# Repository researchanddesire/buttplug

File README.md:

# Buttplug Compass

[Read the illustrated engineering and assembly docs](https://researchanddesire.github.io/buttplug/)

For AJ and other collaborators: start with [the checkpoint handoff](COLLABORATION.md).
It distinguishes the saved threaded-stub CAD from unresolved locking/tooling choices.

Compass is a smart plug and charging dock. The device is a turned stainless
steel body and nose cap with a cast silicone flange. One 52 × 20 mm board in the
flange carries the ESP32-C3, charger, motor driver, temperature sensing and
compass. A protected LiPo and the vibration motor sit in the bulb. The clamshell
dock charges it through four contacts, connects it to a computer over USB, and
has a screen, three buttons and UV-C LEDs.

**Status:** EVT1 design in CAD and KiCad. The current device and dock still
need assembly and bench commissioning. See [Project status](developer-docs/docs/status.md).

| Start here | |
| --- | --- |
| How the device works | [developer-docs/docs/device.md](developer-docs/docs/device.md) |
| Step-by-step assembly | [assembly-docs/assembly-guide.md](assembly-docs/assembly-guide.md) |
| Metal part drawings | [developer-docs/docs/drawings.md](developer-docs/docs/drawings.md) |
| Charging dock | [developer-docs/docs/charging-dock.md](developer-docs/docs/charging-dock.md) |
| Device CAD (FreeCAD scripts, STEP) | [hardware/pcb/evt1/one-board/mech/](https://github.com/researchanddesire/buttplug/blob/backplane/trial/hardware/pcb/evt1/one-board/mech/README.md) |
| Device board (KiCad) | [hardware/pcb/evt1/one-board/](https://github.com/researchanddesire/buttplug/blob/backplane/trial/hardware/pcb/evt1/one-board/README.md) |
| Dock CAD | [hardware/cad/evt1-assembly/evt1-wired/](https://github.com/researchanddesire/buttplug/blob/backplane/trial/hardware/cad/evt1-assembly/evt1-wired/README.md) |
| Firmware | [developer-docs/docs/firmware.md](developer-docs/docs/firmware.md) |
| Requirements | [developer-docs/docs/prd.md](developer-docs/docs/prd.md) |
| Human-owned BOM | [hardware/bom.csv](hardware/bom.csv) |

Use Git history and [archived studies](developer-docs/docs/archive/index.md)
for earlier work.
The docs build automatically when changes land on `main`. See [developer site setup](developer-docs/README.md).

Forked from [researchanddesire/rad-project-template](https://github.com/researchanddesire/rad-project-template).
Repository: `researchanddesire/buttplug`; the local folder keeps its earlier name.
Product release and license selection remain pending. See [LICENSE](LICENSE).

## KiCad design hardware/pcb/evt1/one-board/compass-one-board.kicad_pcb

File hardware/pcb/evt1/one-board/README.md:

# Compass EVT1 device

The compact, four-layer device PCB is 52 × 20 × 1 mm and populated on
both sides. Open [the KiCad project](compass-one-board.kicad_pro) to view the
charger, motor driver, ESP32-C3, sensors, buttons and four dock contacts.
The [FreeCAD assembly](mech/compass-device.FCStd) puts the PCB in a
56 × 32 mm rigid flange and the pack in a removable cradle in the bulb.
Keep the linked parts in the [mechanical source directory](mech/README.md).

| Connector | Function |
| --- | --- |
| J2 | Three-wire protected pack, JST SH. Pins 1 P+, 2 P−, 3 NTC |
| J3 | Motor pair, side-entry JST SH |
| J4 | Bench service and recovery, JST SH |
| J5 | Tip NTC pair, side-entry JST SH |
| CT1–CT4 | Dock GND, D−, D+ and 5 V |

The [BC-PACK-EVT1-002 request](PACK-RFQ.md) calls for one internal 10 kΩ B3435
NTC returned to P−. It feeds the BQ24074 charge-temperature cutoff and U7 AIN2.
The `evt1-one-board` firmware target still uses the former pulsed-divider
acquisition and conversion for AIN2. The shared charger-biased reading
needs implementation and bench validation. The 1 A JST SH rating also needs
reconciliation with the requested 1.5 A continuous pack load.

The [harness sources](../../../cables/evt1/one-board/README.md) define the seven
installed conductors and a separate bench service cable. Their starting stock
lengths come from the CAD wire paths. Check bend radii, crimp retention and
fit on the trial build.

See the [developer and assembly site](https://researchanddesire.github.io/buttplug/)
for the construction drawings, seal sections, assembly sequence and bring-up
plan. Some FreeCAD generation scripts still assume the original checkout path.
The saved native can be opened with its relative part links in place.
The PCB STEP is the mechanical integration model from before the last layout
edits. The compact assembly, mating interface and charging path still need
physical qualification before a fabrication release.

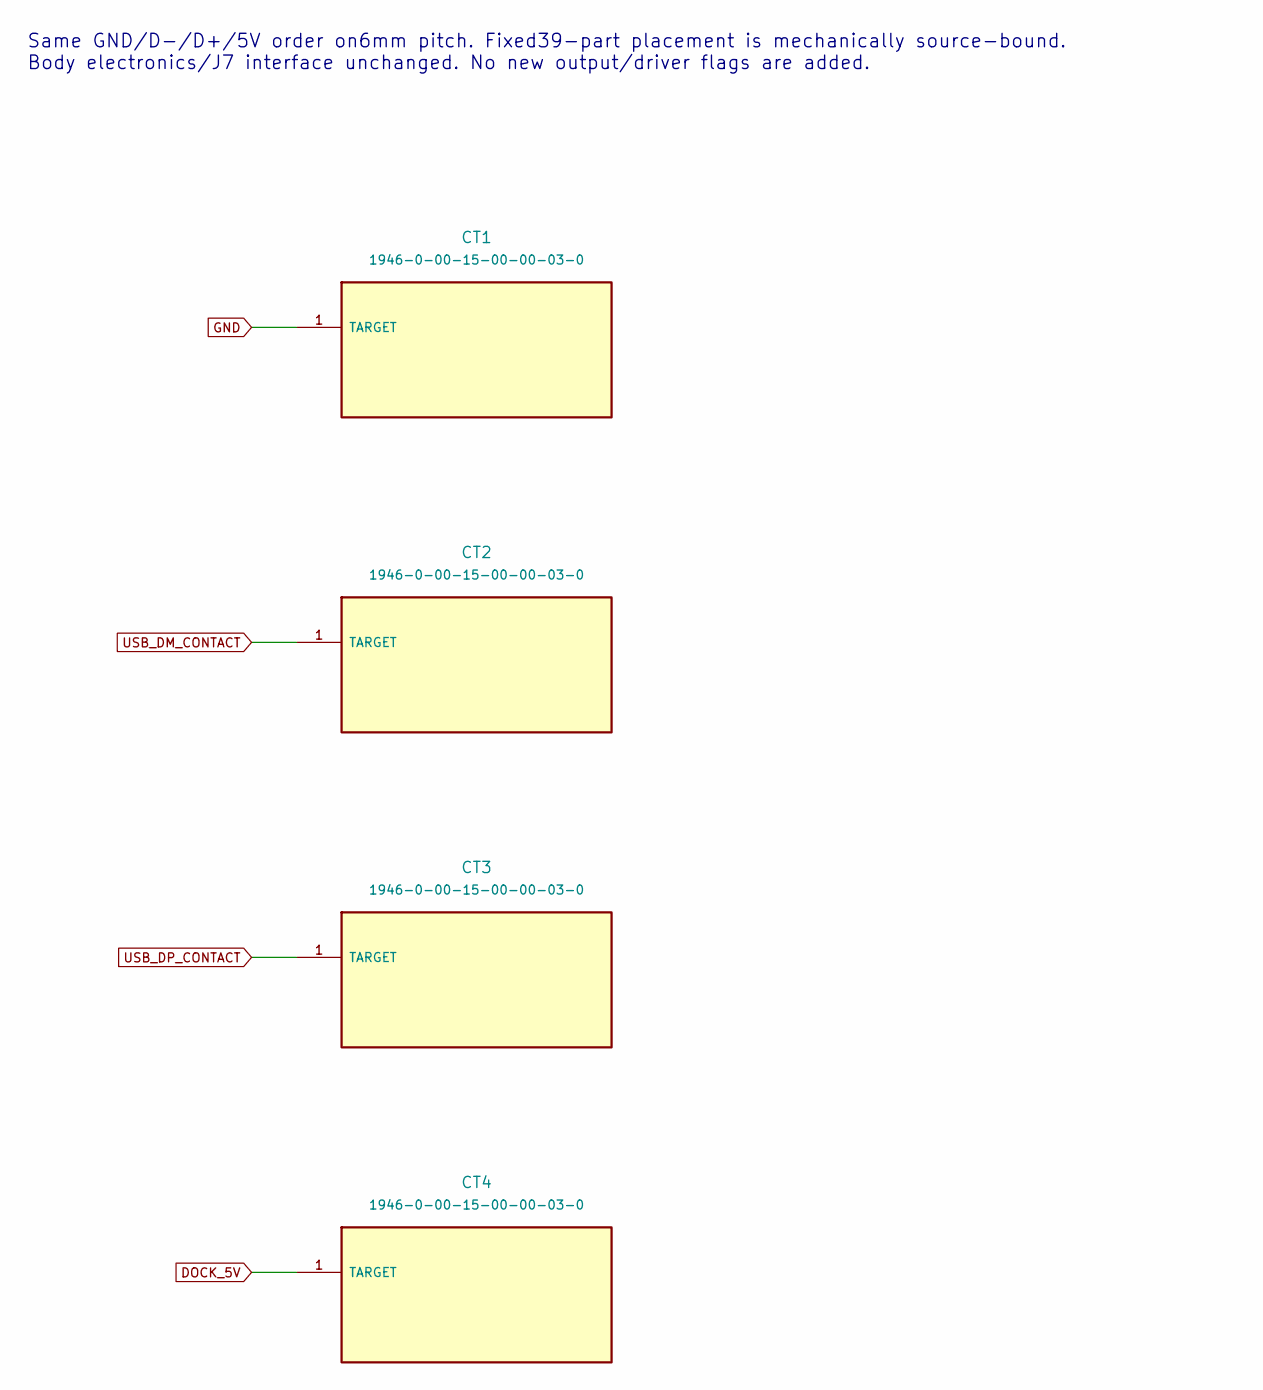
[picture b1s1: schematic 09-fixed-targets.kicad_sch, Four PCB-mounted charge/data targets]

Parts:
CT1, CT2, CT3, CT4: 1946-0-00-15-00-00-03-0; MillMax_1946_0_PTH_Study

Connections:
DOCK_5V: CT4.1; also elsewhere on the board
GND: CT1.1; also elsewhere on the board
USB_DM_CONTACT: CT2.1; also elsewhere on the board
USB_DP_CONTACT: CT3.1; also elsewhere on the board

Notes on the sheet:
Same GND/D−/D+/5V order on6mm pitch. Fixed39-part placement is mechanically source-bound. Body electronics/J7 interface unchanged. No new output/driver flags are added.

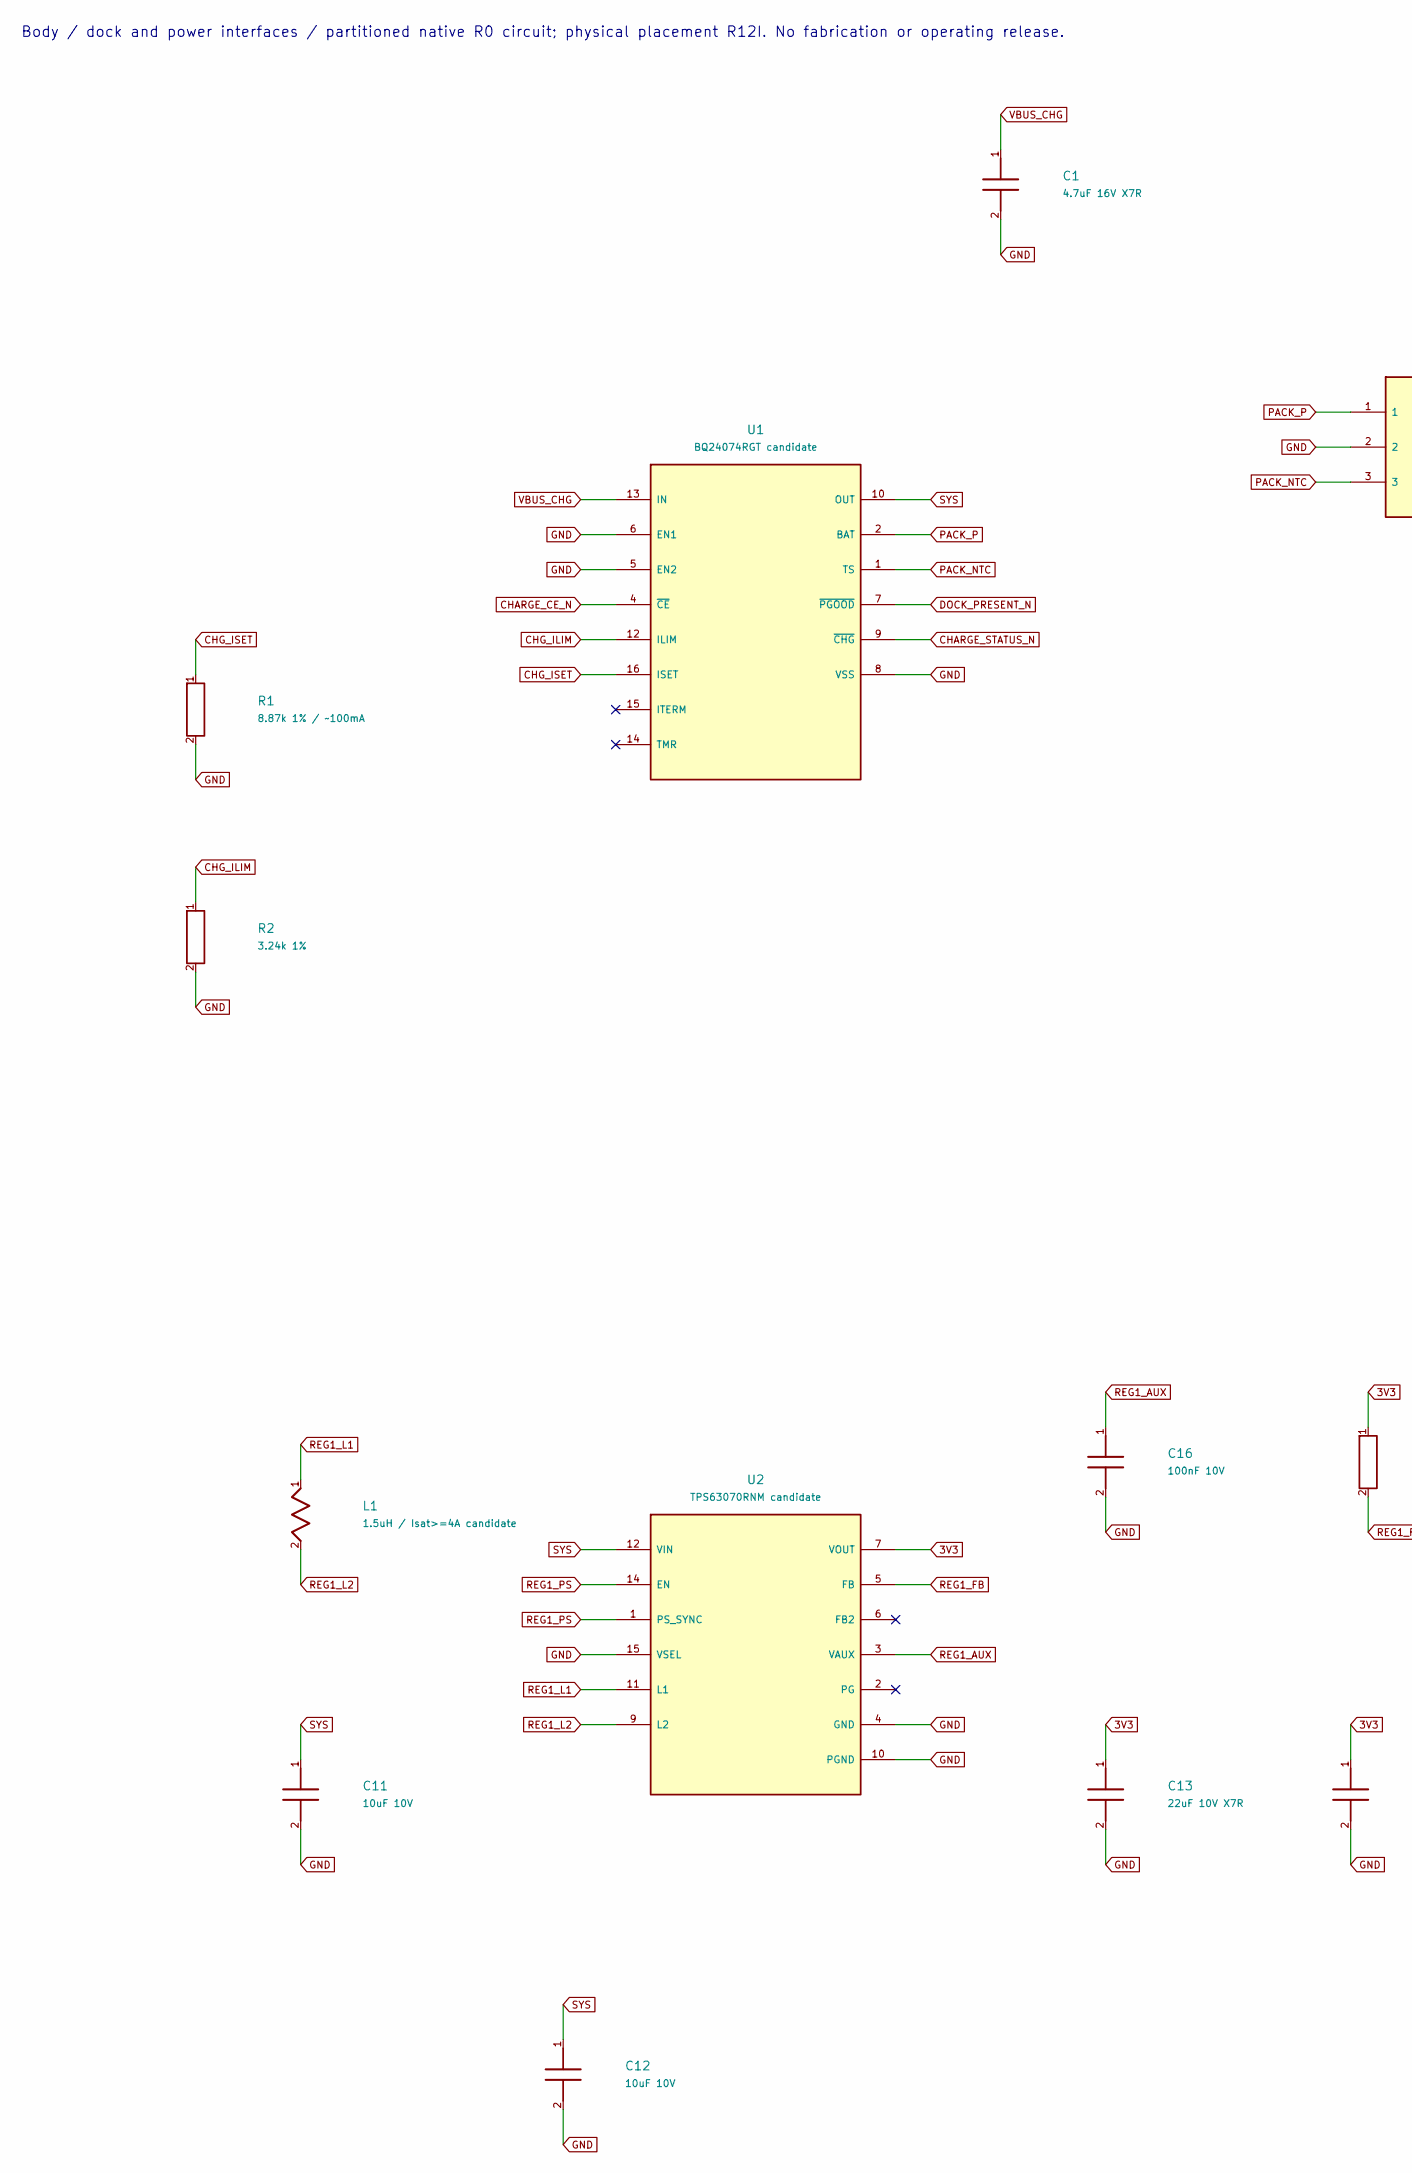
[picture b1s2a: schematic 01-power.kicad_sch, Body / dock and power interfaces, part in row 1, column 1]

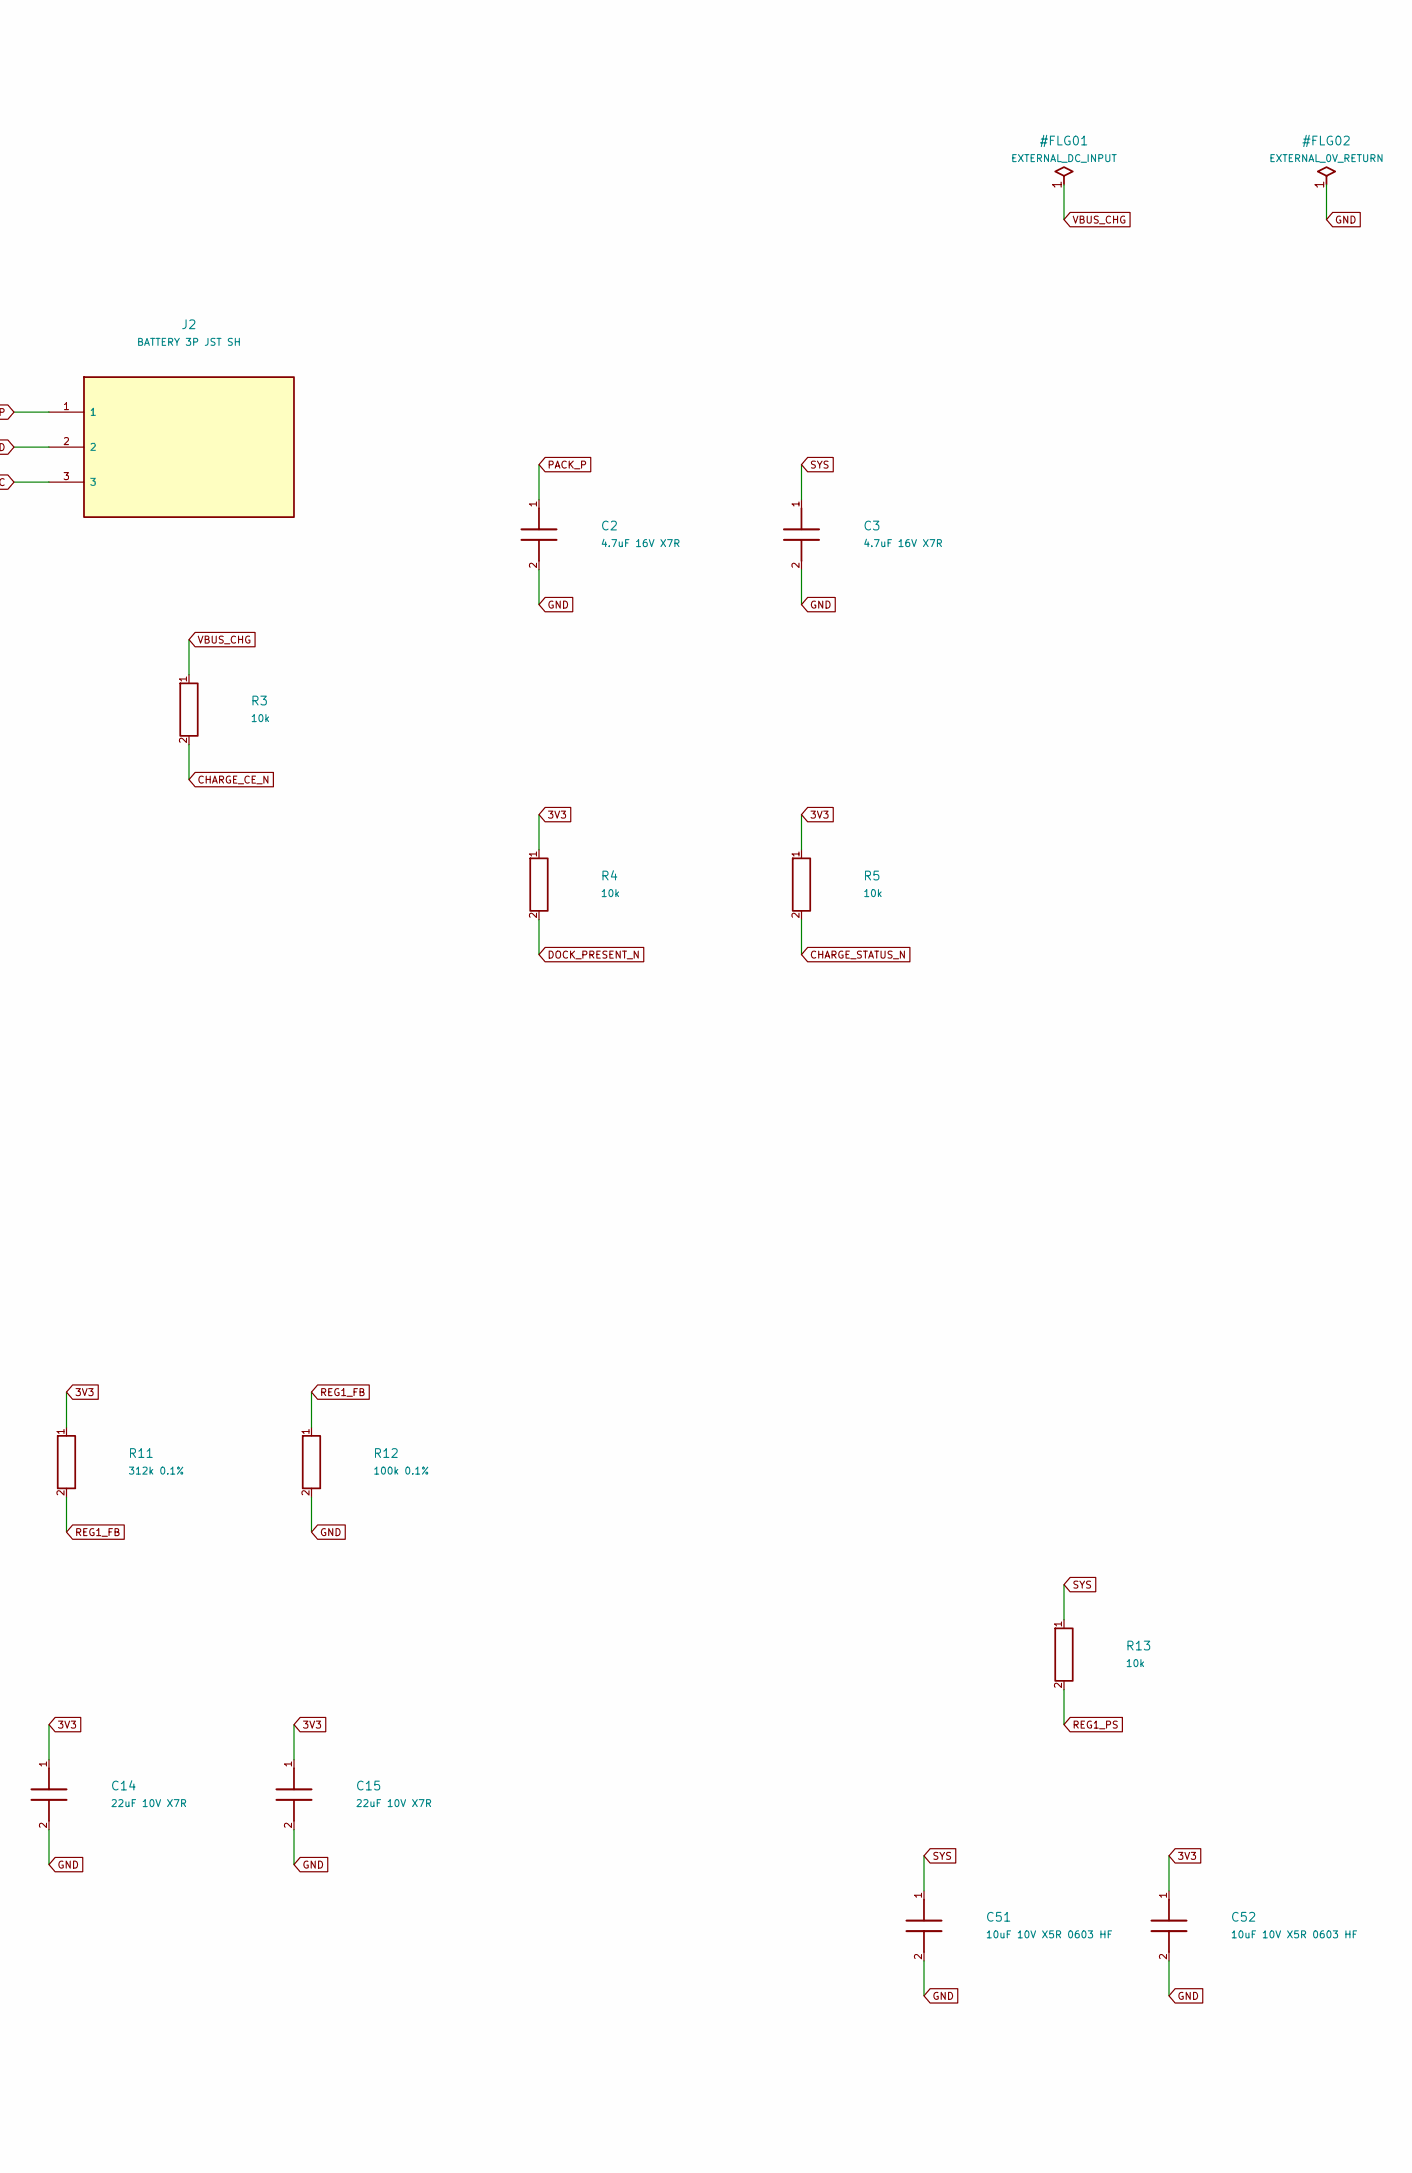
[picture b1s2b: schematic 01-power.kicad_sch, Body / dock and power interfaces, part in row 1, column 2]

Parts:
C1, C2, C3: 4.7uF 16V X7R; Murata_GRM21_0805_Reflow; Manufacturer Part Number GRM21BR71C475KE51L; LCSC Part Number C408144
C11, C12: 10uF 10V; Murata_GRM21_0805_Reflow
C13, C14, C15: 22uF 10V X7R; Murata_GRM31_1206_Reflow
C16: 100nF 10V; Murata_GRM18_0603_Reflow
C51, C52: 10uF 10V X5R 0603 HF; TDK_C1608_0603_Reflow; Manufacturer Part Number CL10A106KP8NNNC; LCSC Part Number C19702
J2: BATTERY 3P JST SH; JST_SH_SM03B-SRSS-TB_1x03-1MP_P1.00mm_Horizontal; Manufacturer Part Number SM03B-SRSS-TB(LF)(SN); LCSC Part Number C160403
L1: 1.5uH / Isat>=4A candidate; L_Coilcraft_XxL4020
R1: 8.87k 1% / ~100mA; R_0402_1005Metric; Manufacturer Part Number TC0210B8871TCC; LCSC Part Number C517790
R2: 3.24k 1%; R_0402_1005Metric; Manufacturer Part Number RT0402BRD073K24L; LCSC Part Number C852760
R3, R4, R5: 10k; R_0402_1005Metric
R11: 312k 0.1%; Vishay_TNPW0603_IEC_Reflow; Manufacturer Part Number RT0603BRD07312KL; LCSC Part Number C861315
R12: 100k 0.1%; Vishay_TNPW0603_IEC_Reflow
R13: 10k; Vishay_TNPW0603_IEC_Reflow
U1: BQ24074RGT candidate; TI_RGT0016C_3x3mm_BQ24074_EP1.68mm
U2: TPS63070RNM candidate; TI_RNM0015A_2.5x3mm_TPS63070

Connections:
3V3: C13.1, C14.1, C15.1, C52.1, R4.1, R5.1, R11.1, U2.7 (VOUT), U2.8 (VOUT); also elsewhere on the board
CHARGE_CE_N: R3.2, U1.4 (~CE); also elsewhere on the board
CHARGE_STATUS_N: R5.2, U1.9 (~CHG)
CHG_ILIM: R2.1, U1.12 (ILIM)
CHG_ISET: R1.1, U1.16 (ISET)
DOCK_PRESENT_N: R4.2, U1.7 (~PGOOD); also elsewhere on the board
GND: C1.2, C2.2, C3.2, C11.2, C12.2, C13.2, C14.2, C15.2, C16.2, C51.2, C52.2, J2.2, R1.2, R2.2, R12.2, U1.5 (EN2), U1.6 (EN1), U1.8 (VSS), U1.17 (EP), U2.4 (GND), U2.10 (PGND), U2.15 (VSEL); also elsewhere on the board
PACK_NTC: J2.3, U1.1 (TS); also elsewhere on the board
PACK_P: C2.1, J2.1, U1.2 (BAT), U1.3 (BAT); also elsewhere on the board
REG1_AUX: C16.1, U2.3 (VAUX)
REG1_FB: R11.2, R12.1, U2.5 (FB)
REG1_L1: L1.1, U2.11 (L1)
REG1_L2: L1.2, U2.9 (L2)
REG1_PS: R13.2, U2.1 (PS_SYNC), U2.14 (EN)
SYS: C3.1, C11.1, C12.1, C51.1, R13.1, U1.10 (OUT), U1.11 (OUT), U2.12 (VIN), U2.13 (VIN); also elsewhere on the board
VBUS_CHG: C1.1, R3.1, U1.13 (IN); also elsewhere on the board

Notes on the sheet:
Body / dock and power interfaces / partitioned native R0 circuit; physical placement R12I. No fabrication or operating release.

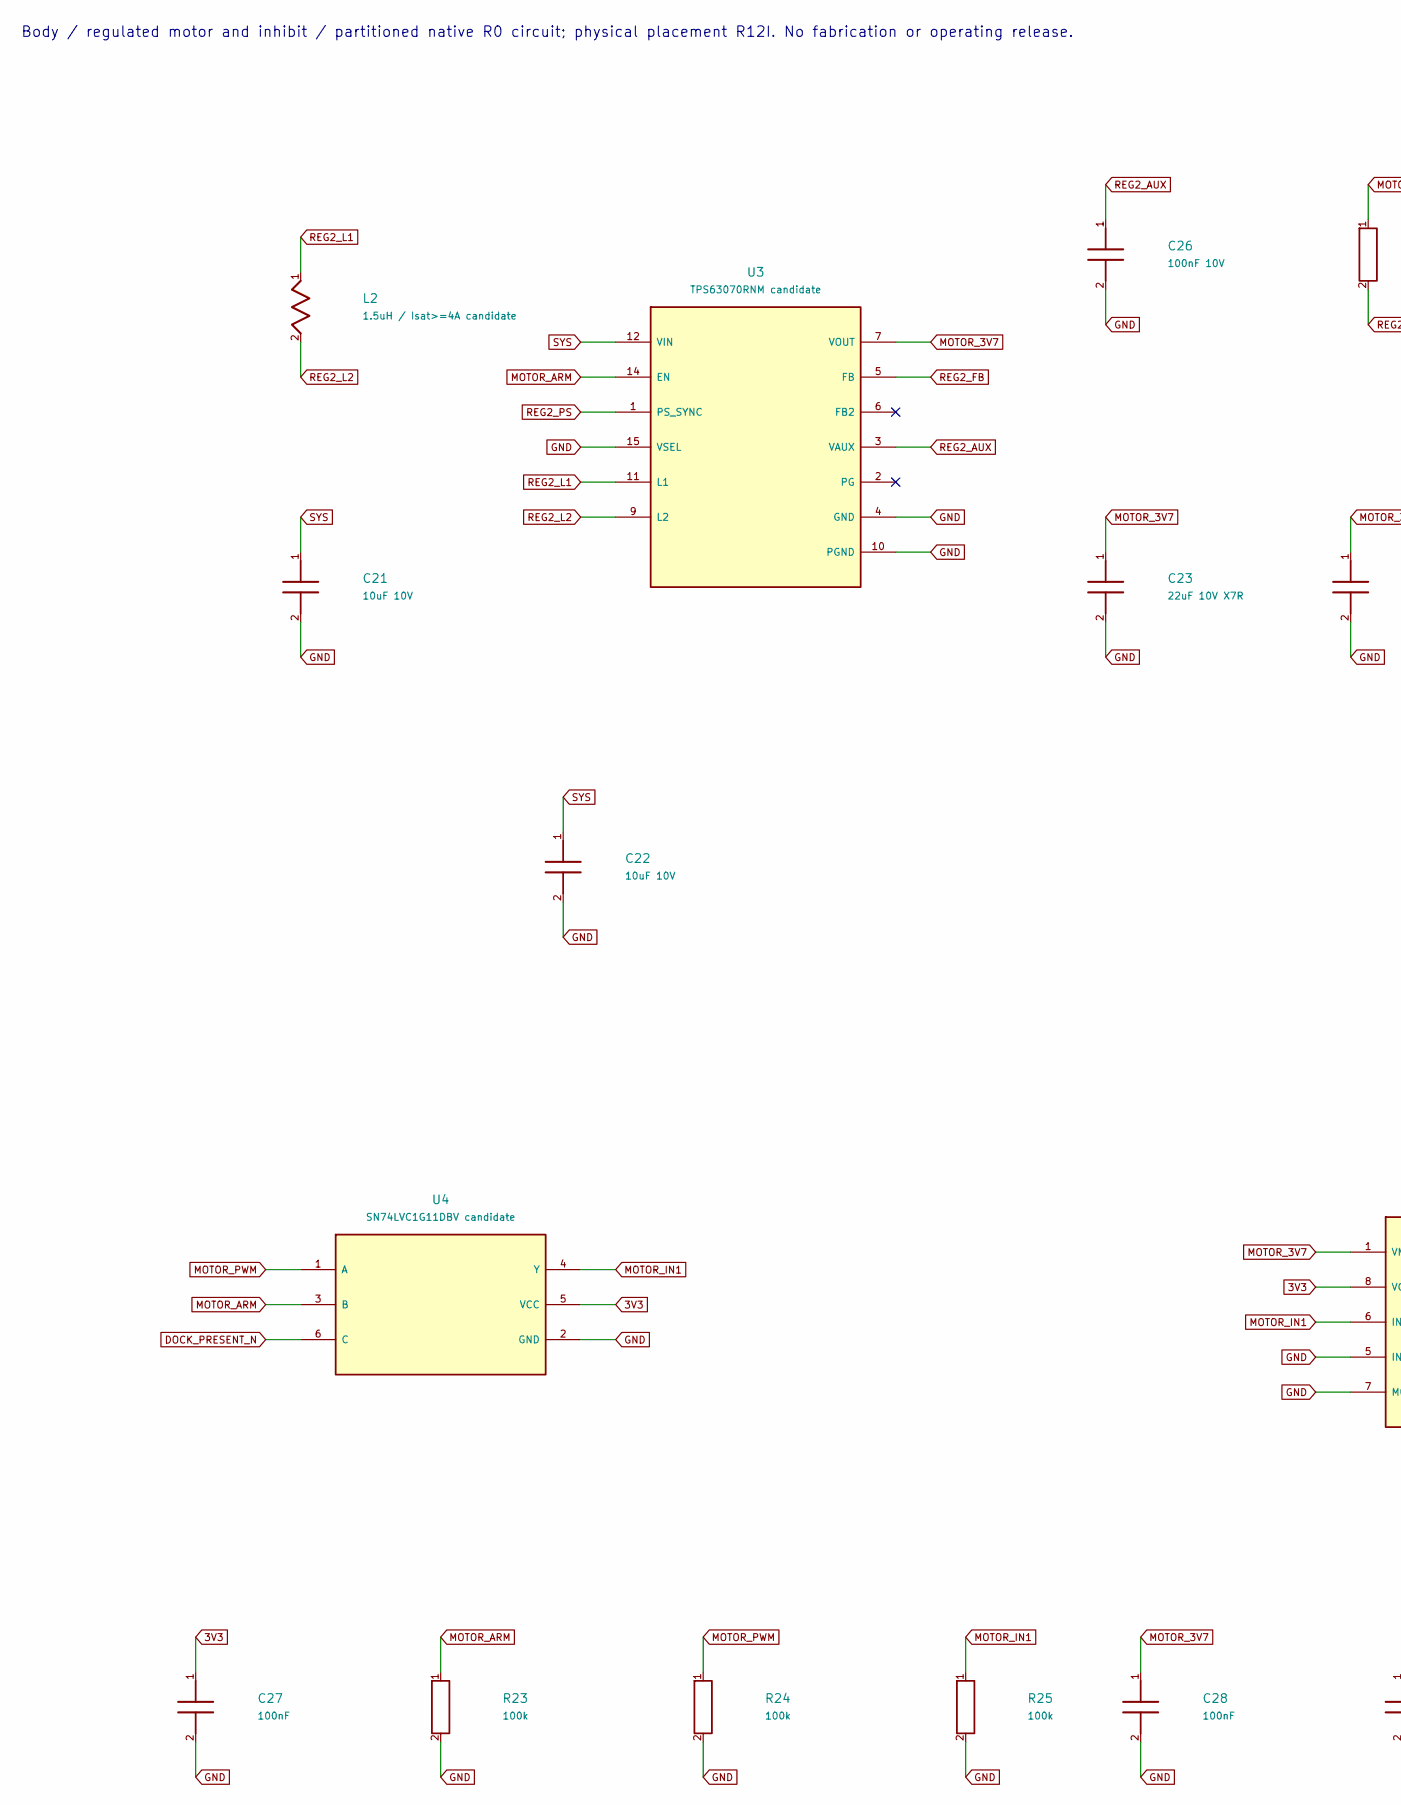
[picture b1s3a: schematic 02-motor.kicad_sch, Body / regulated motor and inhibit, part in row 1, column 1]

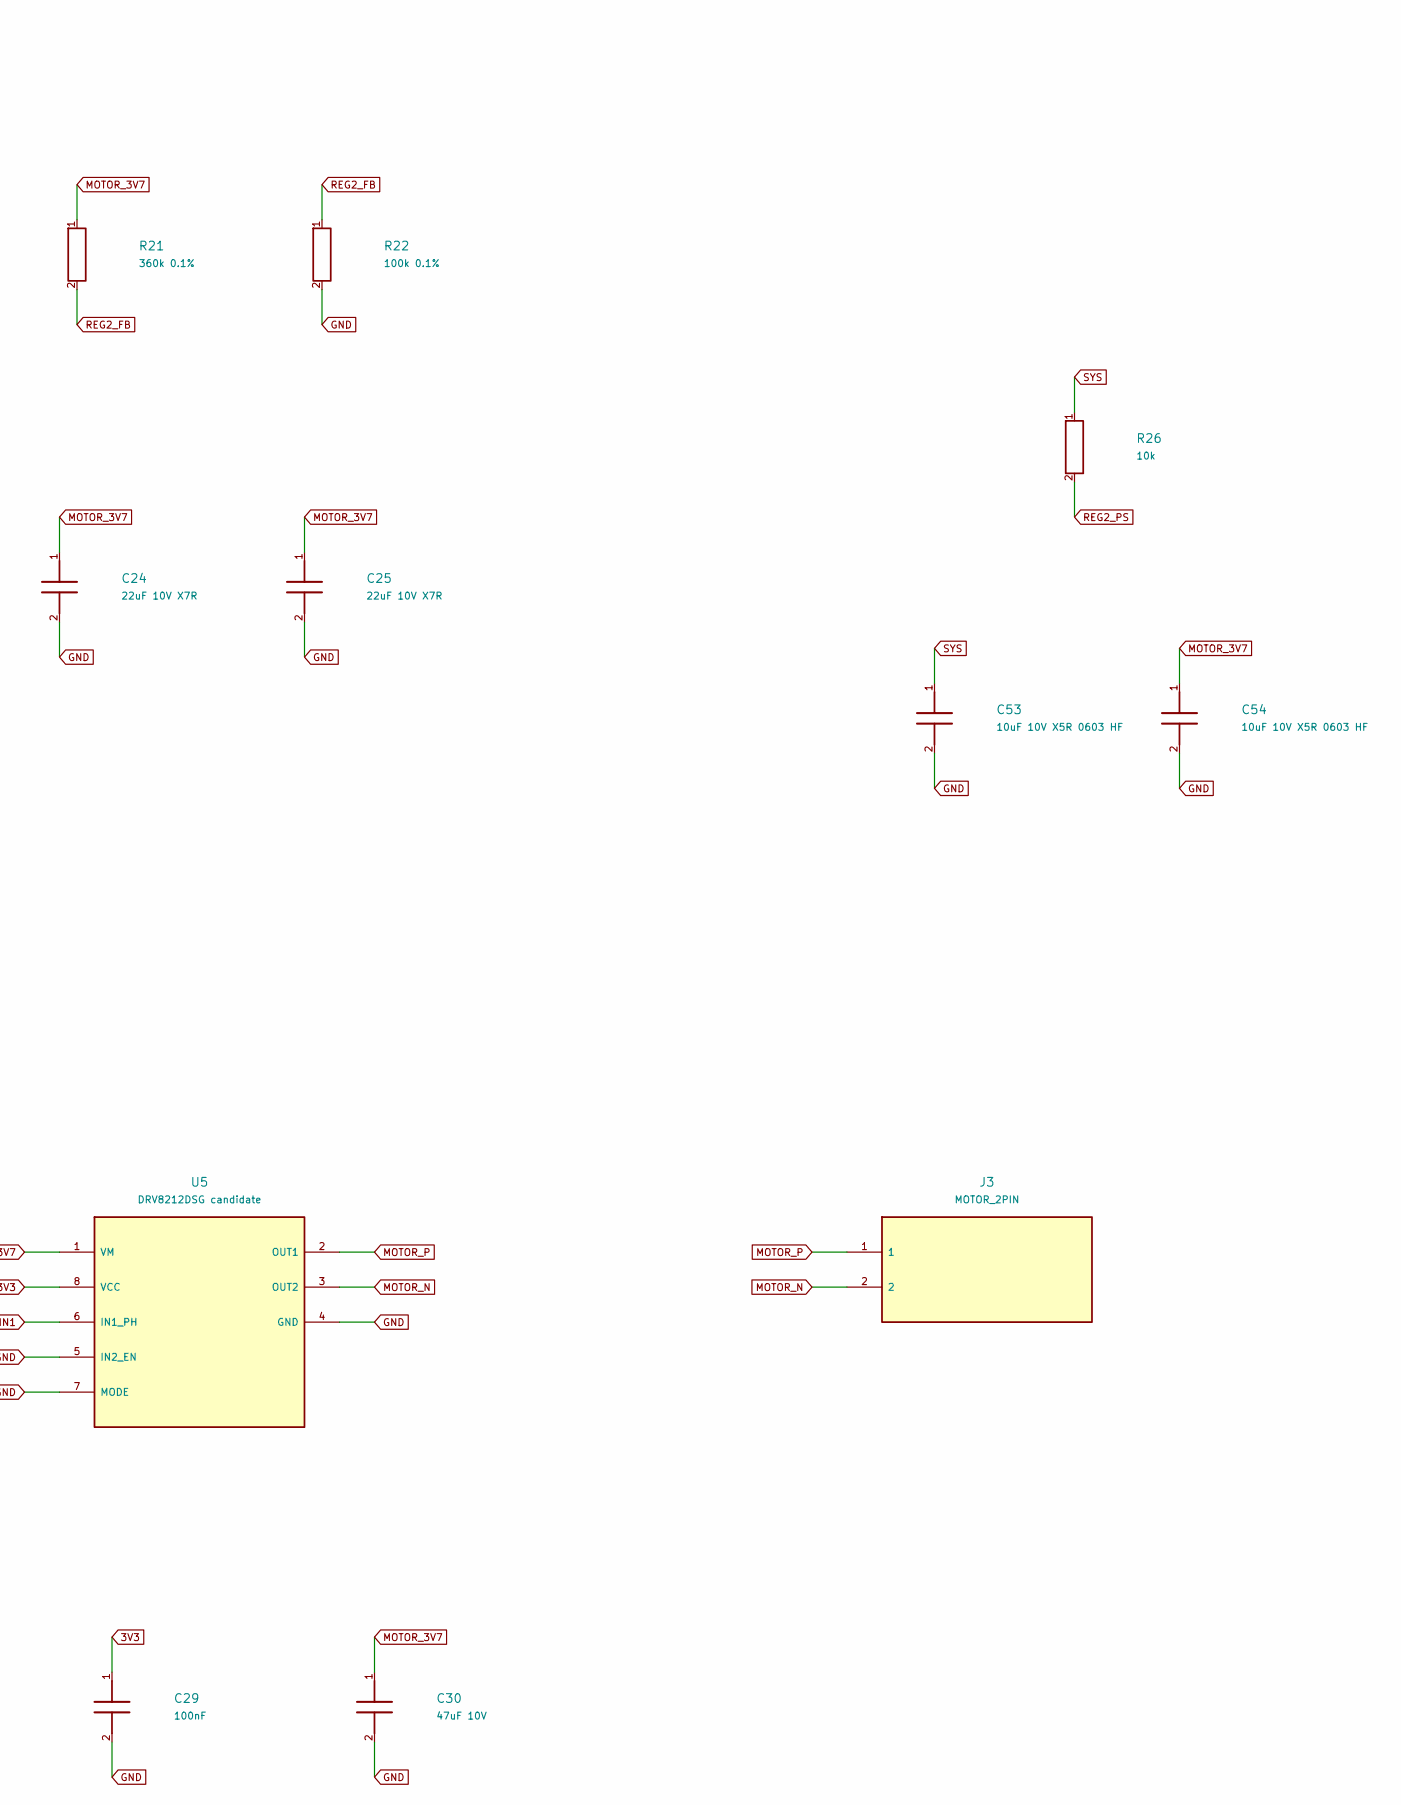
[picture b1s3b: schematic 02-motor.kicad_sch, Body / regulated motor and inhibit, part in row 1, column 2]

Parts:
C21, C22: 10uF 10V; Murata_GRM21_0805_Reflow
C23, C24, C25: 22uF 10V X7R; Murata_GRM31_1206_Reflow
C26: 100nF 10V; Murata_GRM18_0603_Reflow
C27: 100nF; Murata_GRM18_0603_Reflow
C28, C29: 100nF; C_0402_1005Metric
C30: 47uF 10V; Murata_GRM32_1210_Reflow
C53, C54: 10uF 10V X5R 0603 HF; TDK_C1608_0603_Reflow; Manufacturer Part Number CL10A106KP8NNNC; LCSC Part Number C19702
J3: MOTOR_2PIN; JST_SH_SM02B-SRSS-TB_1x02-1MP_P1.00mm_Horizontal
L2: 1.5uH / Isat>=4A candidate; L_Coilcraft_XxL4020
R21: 360k 0.1%; RESI_PTFR0805_C16003; Manufacturer Part Number PTFR0805B360KN9; LCSC Part Number C351576
R22: 100k 0.1%; Vishay_TNPW0603_IEC_Reflow
R23, R24, R25: 100k; R_0402_1005Metric
R26: 10k; Vishay_TNPW0603_IEC_Reflow
U3: TPS63070RNM candidate; TI_RNM0015A_2.5x3mm_TPS63070
U4: SN74LVC1G11DBV candidate; SOT-23-6
U5: DRV8212DSG candidate; WSON-8-1EP_2x2mm_P0.5mm_EP0.9x1.6mm

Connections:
3V3: C27.1, C29.1, U4.5 (VCC), U5.8 (VCC); also elsewhere on the board
DOCK_PRESENT_N: U4.6 (C); also elsewhere on the board
GND: C21.2, C22.2, C23.2, C24.2, C25.2, C26.2, C27.2, C28.2, C29.2, C30.2, C53.2, C54.2, R22.2, R23.2, R24.2, R25.2, U3.4 (GND), U3.10 (PGND), U3.15 (VSEL), U4.2 (GND), U5.4 (GND), U5.5 (IN2_EN), U5.7 (MODE), U5.9 (EP); also elsewhere on the board
MOTOR_3V7: C23.1, C24.1, C25.1, C28.1, C30.1, C54.1, R21.1, U3.7 (VOUT), U3.8 (VOUT), U5.1 (VM)
MOTOR_ARM: R23.1, U3.14 (EN), U4.3 (B); also elsewhere on the board
MOTOR_IN1: R25.1, U4.4 (Y), U5.6 (IN1_PH)
MOTOR_N: J3.2, U5.3 (OUT2)
MOTOR_P: J3.1, U5.2 (OUT1)
MOTOR_PWM: R24.1, U4.1 (A); also elsewhere on the board
REG2_AUX: C26.1, U3.3 (VAUX)
REG2_FB: R21.2, R22.1, U3.5 (FB)
REG2_L1: L2.1, U3.11 (L1)
REG2_L2: L2.2, U3.9 (L2)
REG2_PS: R26.2, U3.1 (PS_SYNC)
SYS: C21.1, C22.1, C53.1, R26.1, U3.12 (VIN), U3.13 (VIN); also elsewhere on the board

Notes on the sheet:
Body / regulated motor and inhibit / partitioned native R0 circuit; physical placement R12I. No fabrication or operating release.

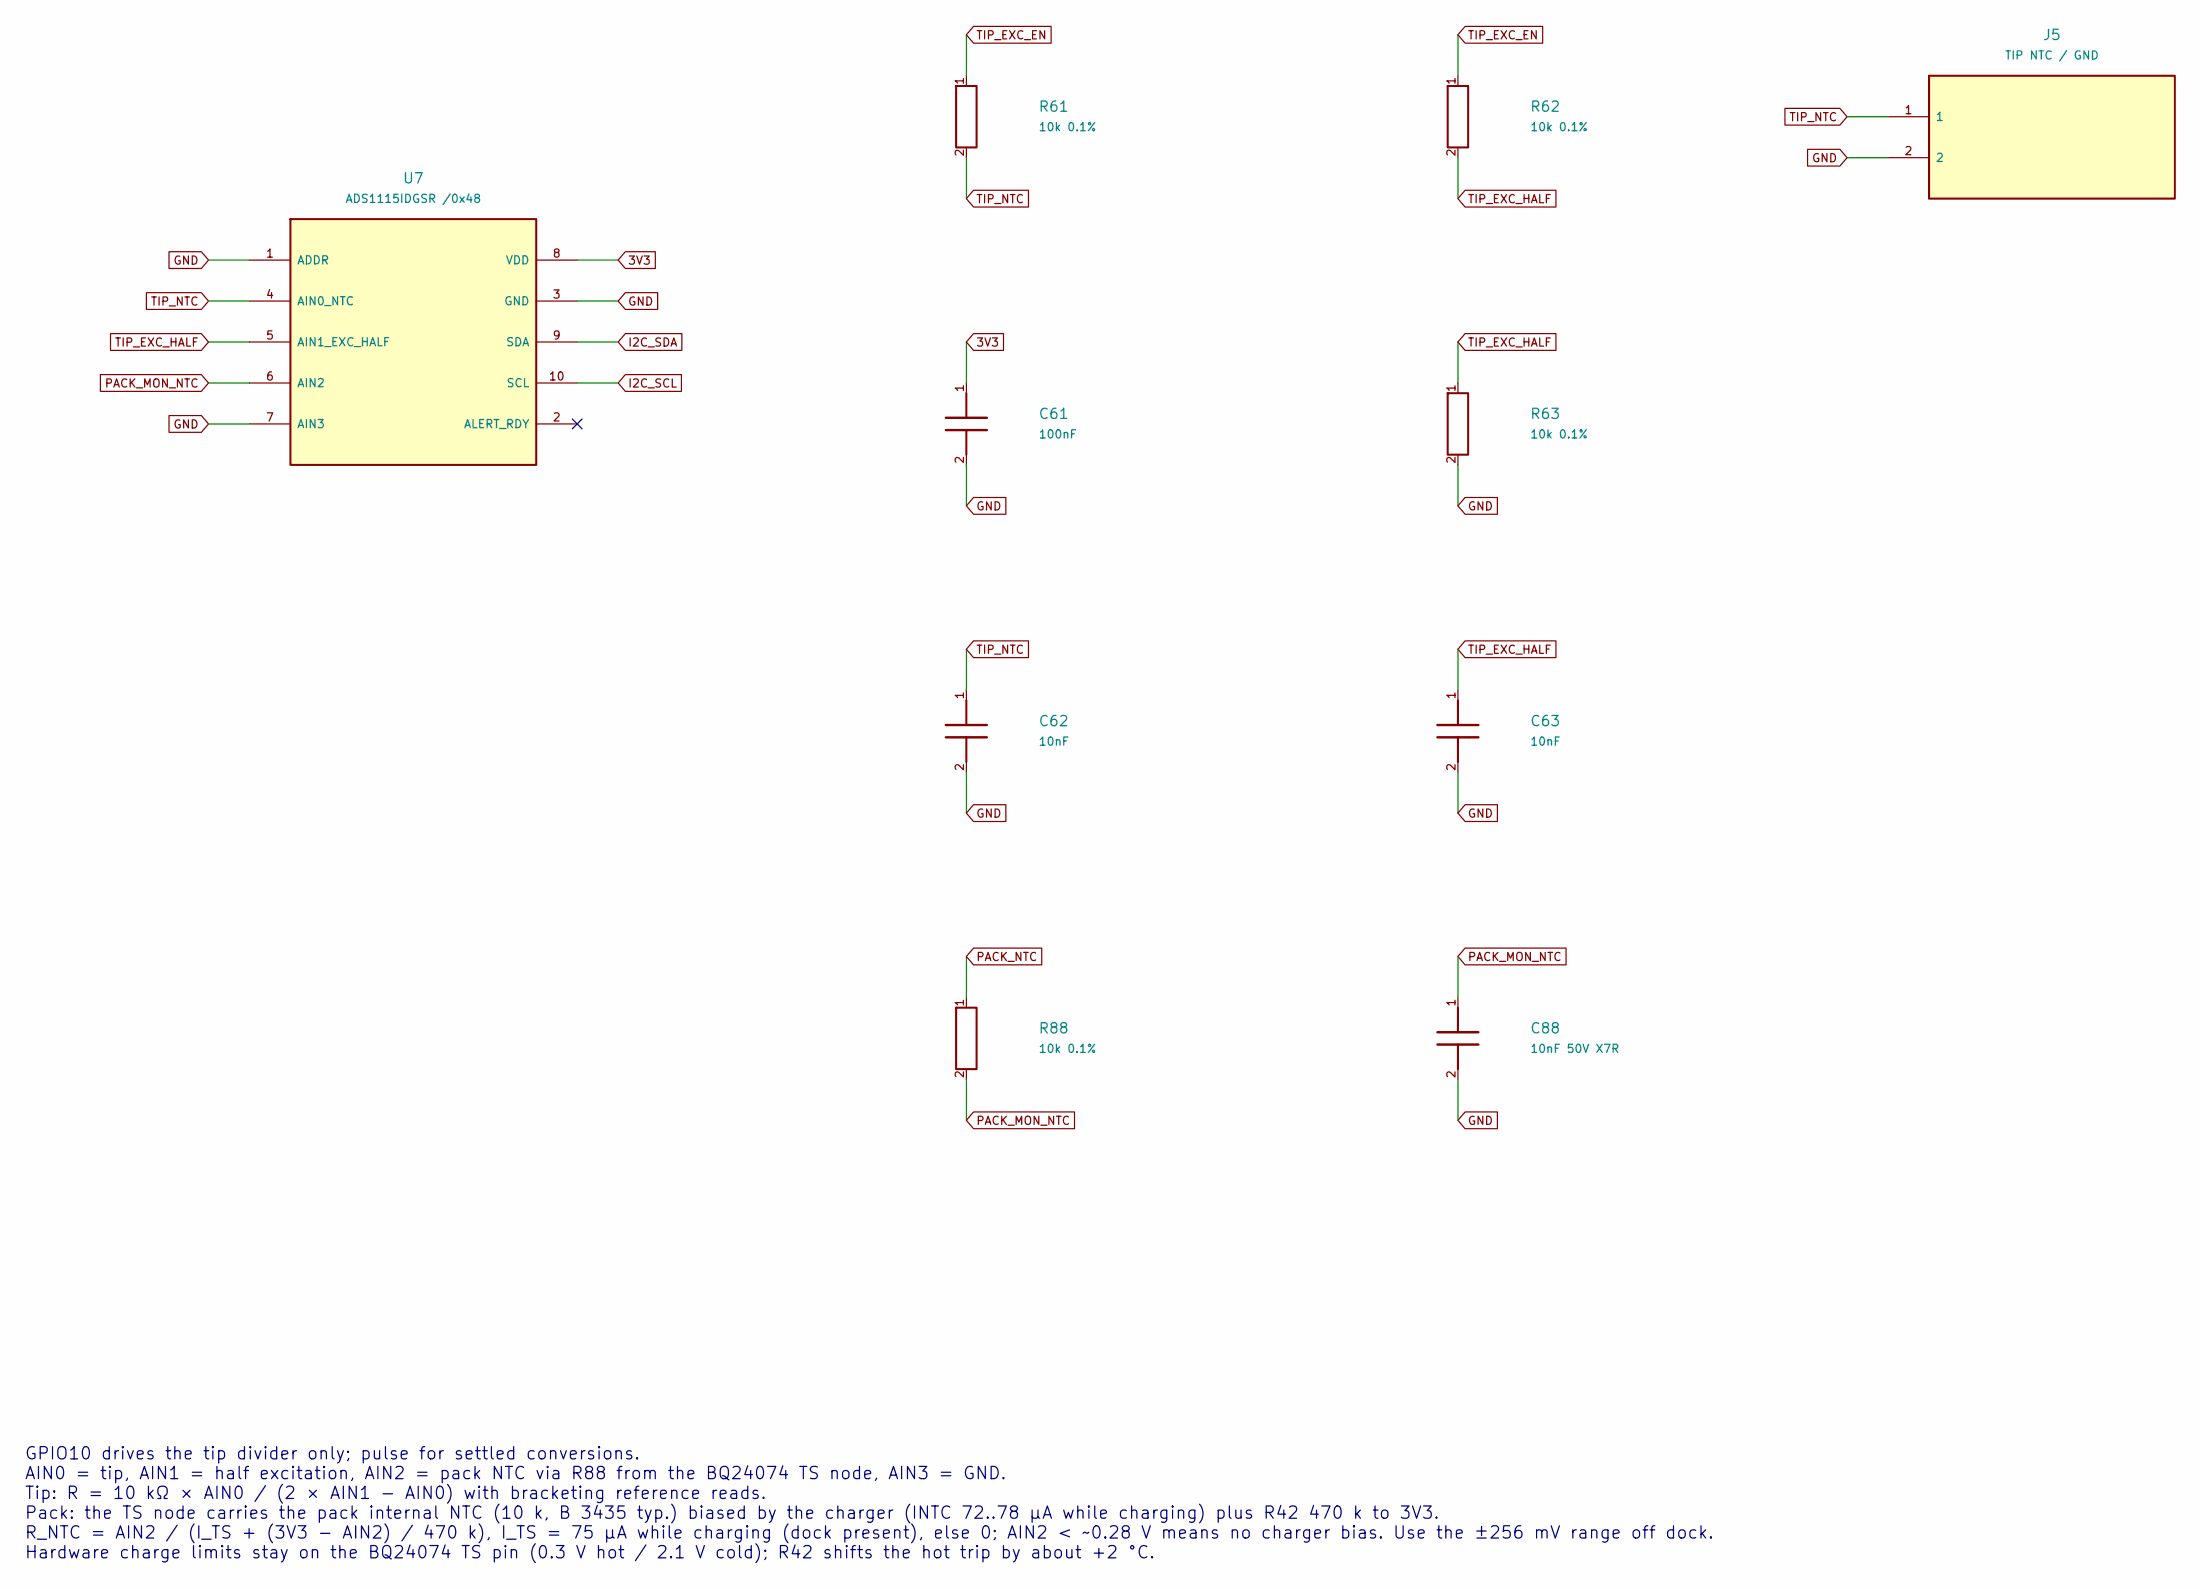
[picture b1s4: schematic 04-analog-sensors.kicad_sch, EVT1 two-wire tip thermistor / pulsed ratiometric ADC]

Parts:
C61: 100nF; C_0402_1005Metric
C62, C63: 10nF; C_0402_1005Metric
C88: 10nF 50V X7R; C_0402_1005Metric; Manufacturer Part Number GRM155R71H103KA88D
J5: TIP NTC / GND; JST_SH_SM02B-SRSS-TB_1x02-1MP_P1.00mm_Horizontal; Manufacturer Part Number SM02B-SRSS-TB(LF)(SN); LCSC Part Number C160402
R61, R62, R63: 10k 0.1%; R_0402_1005Metric
R88: 10k 0.1%; R_0402_1005Metric; Manufacturer Part Number TNPW040210K0BEED
U7: ADS1115IDGSR /0x48; VSSOP-10_3x3mm_P0.5mm

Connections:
3V3: C61.1, U7.8 (VDD); also elsewhere on the board
GND: C61.2, C62.2, C63.2, C88.2, J5.2, R63.2, U7.1 (ADDR), U7.3 (GND), U7.7 (AIN3); also elsewhere on the board
I2C_SCL: U7.10 (SCL); also elsewhere on the board
I2C_SDA: U7.9 (SDA); also elsewhere on the board
PACK_MON_NTC: C88.1, R88.2, U7.6 (AIN2)
PACK_NTC: R88.1; also elsewhere on the board
TIP_EXC_EN: R61.1, R62.1; also elsewhere on the board
TIP_EXC_HALF: C63.1, R62.2, R63.1, U7.5 (AIN1_EXC_HALF)
TIP_NTC: C62.1, J5.1, R61.2, U7.4 (AIN0_NTC)

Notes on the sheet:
GPIO10 drives the tip divider only; pulse for settled conversions. AIN0 = tip, AIN1 = half excitation, AIN2 = pack NTC via R88 from the BQ24074 TS node, AIN3 = GND. Tip: R = 10 kΩ × AIN0 / (2 × AIN1 − AIN0) with bracketing reference reads. Pack: the TS node carries the pack internal NTC (10 k, B 34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
